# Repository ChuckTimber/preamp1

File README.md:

# preamp1

[TCプリアンプ - DIY Fx and Synthesizer](https://scrapbox.io/diyfx/TC%E3%83%97%E3%83%AA%E3%82%A2%E3%83%B3%E3%83%97)

## 回路図

## 動作ビデオ

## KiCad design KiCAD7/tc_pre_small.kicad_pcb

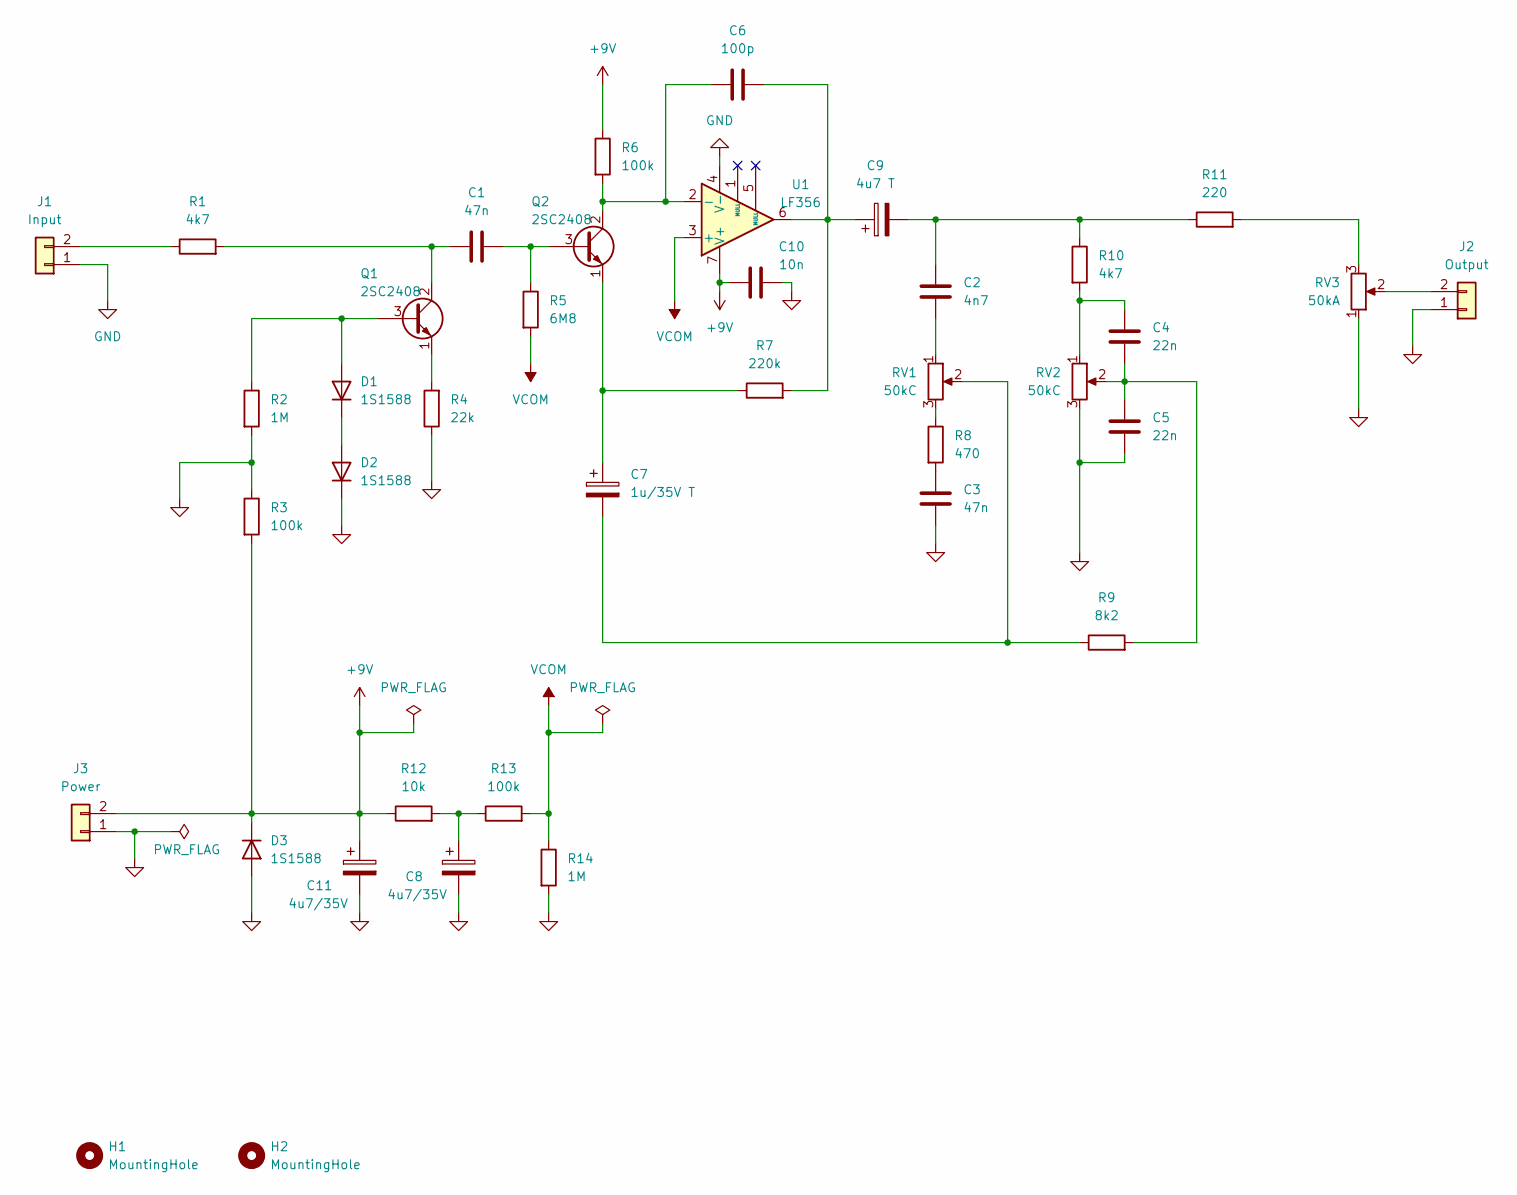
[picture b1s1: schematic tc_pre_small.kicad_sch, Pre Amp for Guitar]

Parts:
C1, C3: 47n; C_Rect_L7.0mm_W2.0mm_P5.00mm
C2: 4n7; C_Disc_D5.0mm_W2.5mm_P5.00mm
C4, C5: 22n; C_Rect_L7.0mm_W3.5mm_P5.00mm
C6: 100p; C_Disc_D5.0mm_W2.5mm_P5.00mm
C7: 1u/35V T; CP_Radial_Tantal_D5.5mm_P5.00mm
C8, C11: 4u7/35V; CP_Radial_D5.0mm_P2.50mm
C9: 4u7 T; CP_Radial_D6.3mm_P2.50mm
C10: 10n; C_Disc_D3.0mm_W2.0mm_P2.50mm
D1, D2, D3: 1S1588; D_A-405_P2.54mm_Vertical_KathodeUp
H1, H2: MountingHole; MountingHole_3.2mm_M3
J1: Input; PinSocket_1x02_P2.54mm_Vertical
J2: Output; PinSocket_1x02_P2.54mm_Vertical
J3: Power; PinSocket_1x02_P2.54mm_Vertical
Q1, Q2: 2SC2408; TO-92_Inline_Wide
R1, R10: 4k7; R_Axial_DIN0207_L6.3mm_D2.5mm_P2.54mm_Vertical
R2, R14: 1M; R_Axial_DIN0207_L6.3mm_D2.5mm_P2.54mm_Vertical
R3, R6, R13: 100k; R_Axial_DIN0207_L6.3mm_D2.5mm_P2.54mm_Vertical
R4: 22k; R_Axial_DIN0207_L6.3mm_D2.5mm_P2.54mm_Vertical
R5: 6M8; R_Axial_DIN0207_L6.3mm_D2.5mm_P2.54mm_Vertical
R7: 220k; R_Axial_DIN0207_L6.3mm_D2.5mm_P2.54mm_Vertical
R8: 470; R_Axial_DIN0207_L6.3mm_D2.5mm_P2.54mm_Vertical
R9: 8k2; R_Axial_DIN0207_L6.3mm_D2.5mm_P2.54mm_Vertical
R11: 220; R_Axial_DIN0207_L6.3mm_D2.5mm_P2.54mm_Vertical
R12: 10k; R_Axial_DIN0207_L6.3mm_D2.5mm_P2.54mm_Vertical
RV1, RV2: 50kC; PinSocket_1x03_P2.54mm_Vertical
RV3: 50kA; PinSocket_1x03_P2.54mm_Vertical
U1: LF356; DIP-8_W7.62mm

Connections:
+9V: C10.2, C11.1, D3.1 (K), J3.2, R3.2, R6.1, R12.1, U1.7 (V+)
GND: C3.1, C5.1, C8.2, C10.1, C11.2, D2.1 (K), D3.2 (A), J1.1, J2.1, J3.1, R2.2, R3.1, R4.1, R14.2, RV2.3, RV3.1, U1.4 (V-)
unnamed: C2.1, RV1.1
unnamed: C2.2, C9.2, R10.1, R11.1
unnamed: C3.2, R8.2
unnamed: C4.1, C5.2, R9.2, RV2.2
unnamed: C4.2, R10.2, RV2.1
unnamed: C6.1, C9.1, R7.2, U1.6
unnamed: C7.2, R9.1, RV1.2
unnamed: C8.1, R12.2, R13.1
unnamed: D1.2 (A), Q1.3 (B), R2.1
unnamed: D1.1 (K), D2.2 (A)
unnamed: J1.2, R1.1
unnamed: J2.2, RV3.2
unnamed: C1.1, Q1.2 (C), R1.2
unnamed: Q1.1 (E), R4.2
unnamed: C1.2, Q2.3 (B), R5.1
unnamed: C6.2, Q2.2 (C), R6.2, U1.2 (-)
unnamed: C7.1, Q2.1 (E), R7.1
unnamed: R8.1, RV1.3
unnamed: R11.2, RV3.3
VCOM: R5.2, R13.2, R14.1, U1.3 (+)

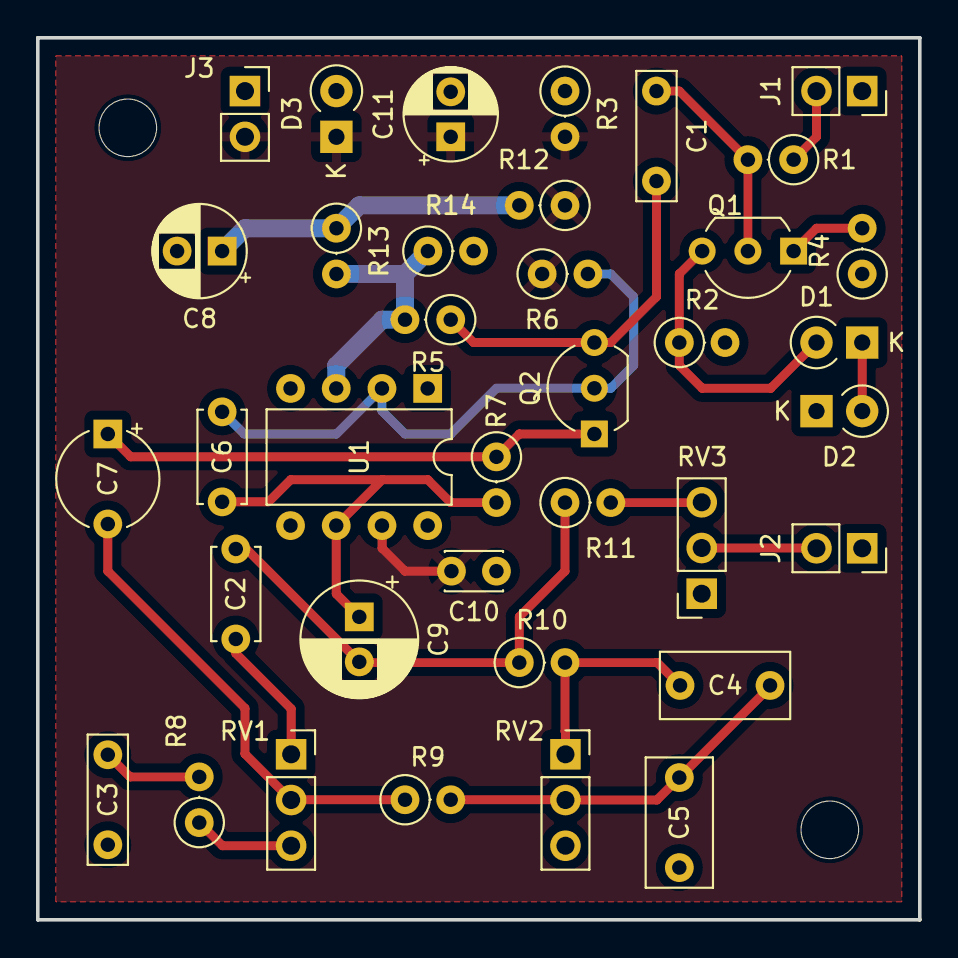
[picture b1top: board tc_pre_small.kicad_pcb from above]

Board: 2 copper layers, 49.0 x 49.0 mm, 39 parts (0 on the bottom side), 22 nets.

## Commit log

2023-12-12 add contents
2023-12-12 Changed contents
2023-12-12 Changed description of README.md
2023-12-12 Changed README.md
2026-01-19 Create LICENSE.md
    Added
